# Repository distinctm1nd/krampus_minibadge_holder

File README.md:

# Krampus Minibadge Holder

The microcontroller is an ATtiny 814. Krampus has a small dev connector with 3V3, GND and the following GPIOs: PA5, PA6, PA7, PB2 and PB3. You can program using the 3-pin sneaky connector (doesn't require soldering). There are multiple ways to program so if you already have your method then you are good to go. If you have not programmed an ATtiny with UDPI then I recommend following the instructions located here to get started: <a href="https://wolles-elektronikkiste.de/en/using-megatinycore">https://wolles-elektronikkiste.de/en/using-megatinycore</a>. If you use the method described here with Arduino, you do not need to connect a resistor in series with pin 6 because this is already installed on the board.

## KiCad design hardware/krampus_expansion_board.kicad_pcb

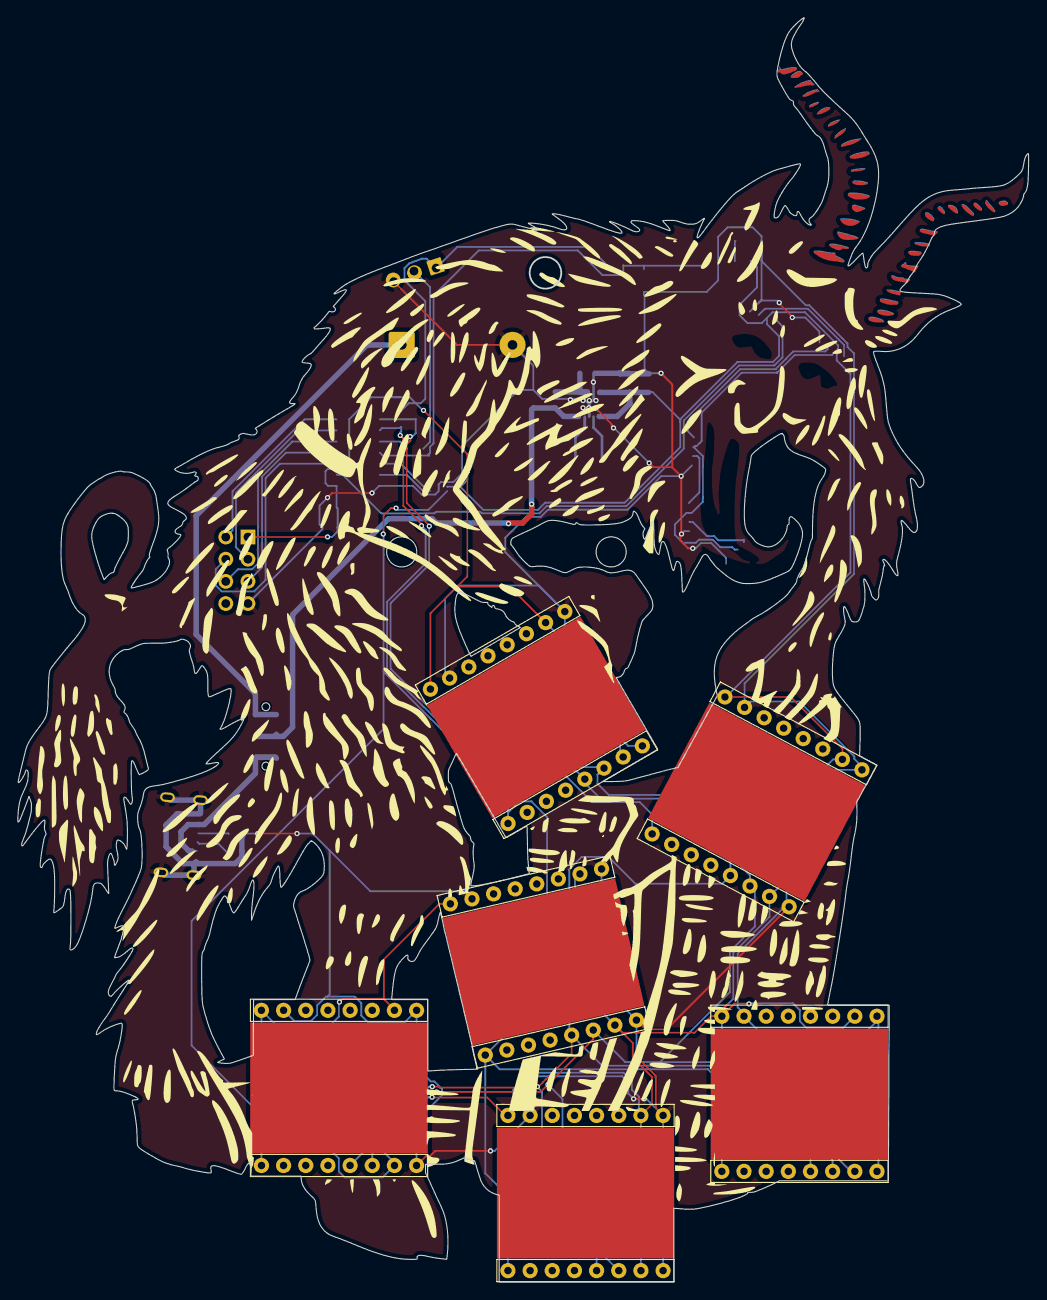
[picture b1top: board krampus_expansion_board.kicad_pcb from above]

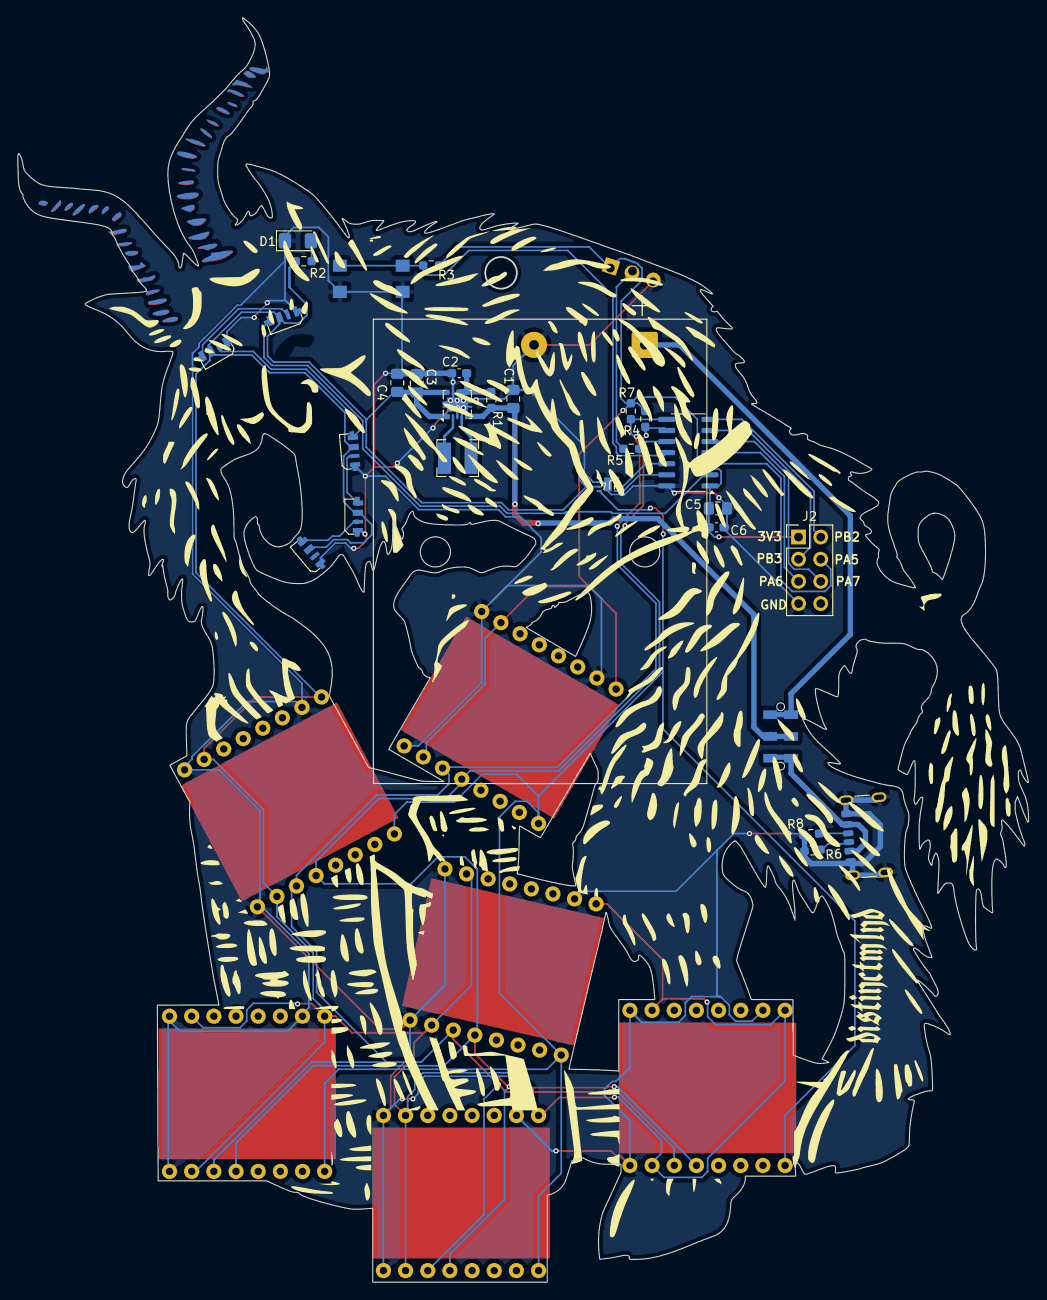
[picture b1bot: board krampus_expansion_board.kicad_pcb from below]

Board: 2 copper layers, 115.7 x 144.8 mm, 36 parts (30 on the bottom side), 29 nets.

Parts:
BT1: Battery; BatteryHolder_Keystone_2479_3xAAA
C1, C3, C4, C5: 10uF; C_0805_2012Metric_Pad1.18x1.45mm_HandSolder
C2, C6: 0.1uF; C_0603_1608Metric_Pad1.08x0.95mm_HandSolder
D1: LED; LED_1206_3216Metric_Pad1.42x1.75mm_HandSolder
D2, D15, D17, D24, D25: WS2812_4020; sk6812-side-a
J1: USB_C_Receptacle_USB2.0_14P; USB_C_Receptacle_GCT_USB4125-xx-x-0190_6P_TopMnt_Horizontal
J2: Conn_01x07_Pin; PinHeader_2x04_P2.54mm_Vertical
J3: Conn_01x03_Pin; night_evil_ai_updi
L1: SRN4018-2R2M; L_Bourns-SRN4018
MB1, MB2, MB3, MB4, MB5, MB6: MiniBadge_Full; MiniBadge_Slot_Reflective
R1: 100 ohm; R_0603_1608Metric_Pad0.98x0.95mm_HandSolder
R2: 15 ohm; R_0603_1608Metric_Pad0.98x0.95mm_HandSolder
R3: 100k ohm; R_0603_1608Metric_Pad0.98x0.95mm_HandSolder
R4, R7: 4.7k ohm; R_0603_1608Metric_Pad0.98x0.95mm_HandSolder
R5: 220 ohm; R_0603_1608Metric_Pad0.98x0.95mm_HandSolder
R6, R8: 5.1k; R_0603_1608Metric_Pad0.98x0.95mm_HandSolder
SW1: SW_DPDT; js202011jaqn
SW2: SW_Push; button_switch_TL3305A
U1: ATtiny814-SS; SOIC-14_3.9x8.7mm_P1.27mm
U3: TPS63001DRCR; Texas_DRC0010J
U4: A3910EEETR-T; DFN-8_ALM

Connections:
+3V3: C3.1, C4.1, C5.1, C6.1, D2.2 (VDD), D15.2 (VDD), D17.2 (VDD), D24.2 (VDD), D25.2 (VDD), J2.1, J3.1, MB1.1 (+VBATT), MB1.7 (+3V3), MB1.15 (3V3+), MB2.1 (+VBATT), MB2.7 (+3V3), MB2.15 (3V3+), MB3.1 (+VBATT), MB3.7 (+3V3), MB3.15 (3V3+), MB4.1 (+VBATT), MB4.7 (+3V3), MB4.15 (3V3+), MB5.1 (+VBATT), MB5.7 (+3V3), MB5.15 (3V3+), MB6.1 (+VBATT), MB6.7 (+3V3), MB6.15 (3V3+), R2.1, R3.1, R4.1, R7.1, U1.1 (VCC), U3.1 (VOUT), U3.10 (FB), U4.7 (VBB)
BATT: BT1.1 (+), SW1.3 (C)
BUTTON: R3.2, SW2.1, U1.11 (PA1)
GND: BT1.2 (-), C1.2, C2.2, C3.2, C4.2, C5.2, C6.2, D1.1 (K), D2.4 (VSS), D15.4 (VSS), D17.4 (VSS), D24.4 (VSS), D25.4 (VSS), J1.A12 (GND), J1.B12 (GND), J1.S1 (SHIELD), J2.7, J3.3, MB1.2 (GND), MB1.8 (GND), MB1.16 (GND), MB2.2 (GND), MB2.8 (GND), MB2.16 (GND), MB3.2 (GND), MB3.8 (GND), MB3.16 (GND), MB4.2 (GND), MB4.8 (GND), MB4.16 (GND), MB5.2 (GND), MB5.8 (GND), MB5.16 (GND), MB6.2 (GND), MB6.8 (GND), MB6.16 (GND), R6.1, R8.1, SW2.2, U1.14 (GND), U3.3 (PGND), U3.9 (GND), U3.11 (PAD), U4.6 (GND), U4.9 (EPAD)
LED_ARRAY: D15.1 (DIN), U1.2 (PA4)
MB_CLOCK: MB1.9 (CLK), MB2.9 (CLK), MB3.9 (CLK), MB4.9 (CLK), MB5.9 (CLK), MB6.9 (CLK), U4.8 (OUT1)
MB_CLOCK_H: U1.13 (PA3), U4.1 (HIN1)
MB_CLOCK_L: U1.12 (PA2), U4.2 (LIN1)
unnamed: D1.2 (A), R2.2
unnamed: D2.1 (DIN), D25.3 (DOUT)
unnamed: D15.3 (DOUT), D17.1 (DIN)
unnamed: D17.3 (DOUT), D24.1 (DIN)
unnamed: D24.3 (DOUT), D25.1 (DIN)
unnamed: J1.A5 (CC1), R6.2
unnamed: J1.B5 (CC2), R8.2
unnamed: C1.1, R1.1, SW1.2 (B), U3.5 (VIN)
unnamed: R5.2, U1.10 (~RESET/PA0)
unnamed: C2.1, R1.2, U3.6 (EN), U3.7 (PS_SYNC), U3.8 (VINA)
unnamed: L1.1, U3.4 (L1)
unnamed: L1.2, U3.2 (L2)
PA5: J2.4, U1.3 (PA5)
PA6: J2.5, U1.4 (PA6)
PA7: J2.6, U1.5 (PA7)
PB2: J2.2, U1.7 (PB2)
PB3: J2.3, U1.6 (PB3)
SCL: MB1.13 (SCL), MB2.13 (SCL), MB3.13 (SCL), MB4.13 (SCL), MB5.13 (SCL), MB6.13 (SCL), R4.2, U1.9 (PB0)
SDA: MB1.14 (SDA), MB2.14 (SDA), MB3.14 (SDA), MB4.14 (SDA), MB5.14 (SDA), MB6.14 (SDA), R7.2, U1.8 (PB1)
UPDI: J3.2, R5.1
VBUS: J1.A9 (VBUS), J1.B9 (VBUS), SW1.1 (A)

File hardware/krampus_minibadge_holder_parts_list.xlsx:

Designator | Footprint | Value | Description | Manufacturer | Supplier | Part Number | Package | First Option
BT1 | BatteryHolder_Keystone_2479_3xAAA | Battery |  |  | Mouser |  |  | https://www.mouser.com/ProductDetail/Keystone-Electronics/24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
C1, C3, C4, C5 | 805 | 10uF |  |  | Mouser |  |  | https://www.mouser.com/ProductDetail/Samsung-Electro-Mechani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
C2, C6 | 603 | 0.1uF |  |  | Mouser |  |  | https://www.mouser.com/ProductDetail/YAGEO/CC0603KRX5R9BB104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
D1 | 1206 | LED
D15, D17, D2, D24, D25 | sk6812-side-a | WS2812_4020 |  |  | LCSC |  |  | https://www.lcsc.com/product-detail/C5378721.html
J1 | USB_C_Receptacle_GCT_USB4125-xx-x-0190_6P_TopMnt_Horizontal | USB_C_Receptacle_USB2.0_14P |  |  | Mouser |  |  | https://www.mouser.com/ProductDetail/GCT/USB4125-GF-A-0190?q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
J2 | PinHeader_2x04_P2.54mm_Vertical |  | No Part Provided- for opt dev
J3 | night_evil_ai_updi | Conn_01x03_Pin | No Part Provided- for programming |  | None
L1 | L_Bourns-SRN4018 | SRN4018-2R2M |  |  | Mouser |  |  | https://www.mouser.com/ProductDetail/Bourns/SRN4018-2R2M?qs=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
MB1, MB2, MB3, MB4, MB5, MB6 | MiniBadge_Slot_Reflective | MiniBadge_Full | 1x8 2.54 female header |  | Tayda
R1 | 0.0603 | 100 ohm
R2 | 0.0603 | 100 ohm
R3 | 0.0603 | 100k ohm
R4, R7 | 0.0603 | 4.7k ohm
R5 | 0.0603 | 220 ohm
R6, R8 | 0.0603 | 5.1k
SW1 | js202011jaqn | SW_DPDT |  |  | Digikey |  |  | https://www.digikey.com/en/products/detail/c-k/JS202011JAQN/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
SW2 | button_switch_TL3305A | SW_Push |  |  | Mouser |  |  | https://www.mouser.com/ProductDetail/E-Switch/TL3305AF160QG?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
U1 | SOIC-14_3.9x8.7mm_P1.27mm | ATtiny814-SS |  |  | Mouser |  |  | https://www.mouser.com/ProductDetail/Microchip-Technology/AT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
U3 | Texas_DRC0010J | TPS63001DRCR |  |  | Mouser |  |  | https://www.mouser.com/ProductDetail/Texas-Instruments/TPS63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
U4 | DFN-8_ALM | A3910EEETR-T |  |  |  |  |  | https://www.mouser.com/ProductDetail/Allegro-MicroSystems/A3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
PCBs |  |  | PCB | JLCPCB | JLCPCB

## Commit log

2025-10-20 Create delete
2025-10-20 Create d
